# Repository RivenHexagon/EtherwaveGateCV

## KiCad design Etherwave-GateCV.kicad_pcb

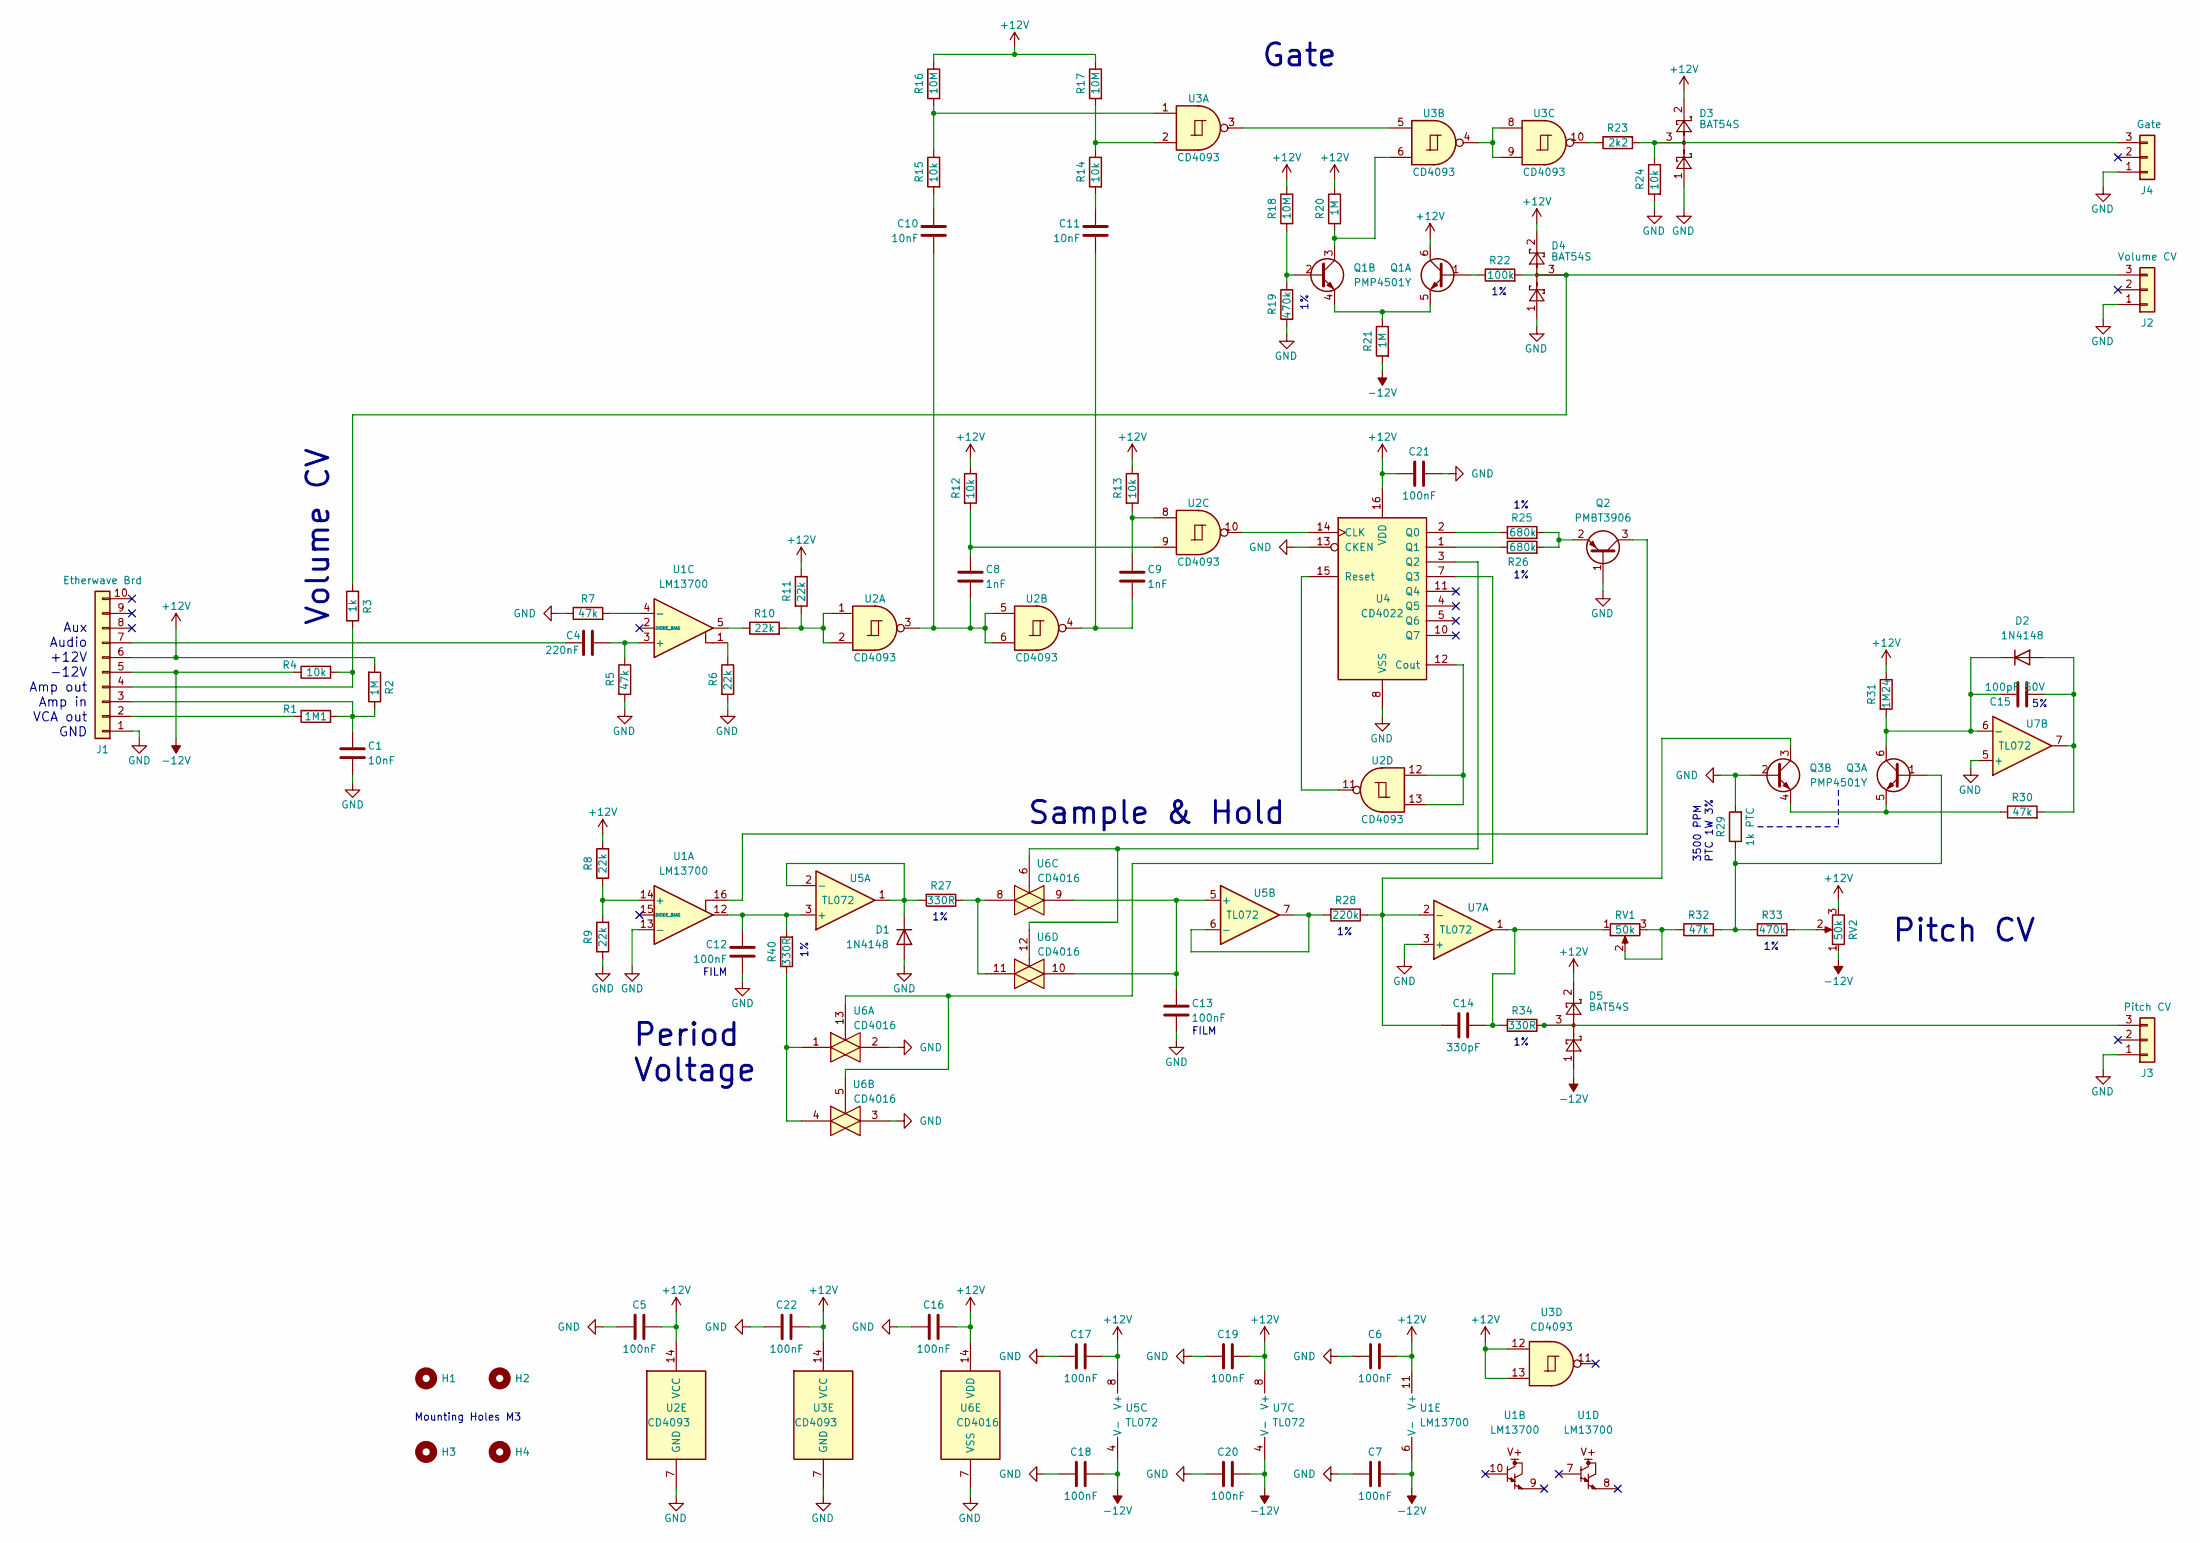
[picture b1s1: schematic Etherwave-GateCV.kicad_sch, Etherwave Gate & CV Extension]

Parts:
C1, C10, C11: 10nF; C_0603_1608Metric_Pad1.08x0.95mm_HandSolder
C4: 220nF; C_0603_1608Metric_Pad1.08x0.95mm_HandSolder
C5, C6, C7, C16, C17, C18, C19, C20, C21, C22: 100nF; C_0603_1608Metric_Pad1.08x0.95mm_HandSolder
C8, C9: 1nF; C_0603_1608Metric_Pad1.08x0.95mm_HandSolder
C12, C13: 100nF; C_1812_4532Metric_Pad1.57x3.40mm_HandSolder
C14: 330pF; C_0603_1608Metric_Pad1.08x0.95mm_HandSolder
C15: 100pF 50V; C_0603_1608Metric_Pad1.08x0.95mm_HandSolder
D1, D2: 1N4148; D_SOD-323_HandSoldering
D3, D4, D5: BAT54S; SOT-23
H1, H2, H3, H4: MountingHole; MountingHole_3.2mm_M3_DIN965
J1: Etherwave Brd; Molex_KK-254_AE-6410-10A_1x10_P2.54mm_Vertical
J2: Volume CV; Molex_KK-254_AE-6410-03A_1x03_P2.54mm_Vertical
J3: Pitch CV; Molex_KK-254_AE-6410-03A_1x03_P2.54mm_Vertical
J4: Gate; Molex_KK-254_AE-6410-03A_1x03_P2.54mm_Vertical
Q1, Q3: PMP4501Y; SOT-363_SC-70-6_Handsoldering
Q2: PMBT3906; SOT-23_Handsoldering
R1: 1M1; R_0603_1608Metric_Pad0.98x0.95mm_HandSolder
R2, R20, R21: 1M; R_0603_1608Metric_Pad0.98x0.95mm_HandSolder
R3: 1k; R_0603_1608Metric_Pad0.98x0.95mm_HandSolder
R4, R12, R13, R14, R15, R24: 10k; R_0603_1608Metric_Pad0.98x0.95mm_HandSolder
R5, R7, R30, R32: 47k; R_0603_1608Metric_Pad0.98x0.95mm_HandSolder
R6, R8, R9, R10, R11: 22k; R_0603_1608Metric_Pad0.98x0.95mm_HandSolder
R16, R17, R18: 10M; R_0603_1608Metric_Pad0.98x0.95mm_HandSolder
R19, R33: 470k; R_0603_1608Metric_Pad0.98x0.95mm_HandSolder
R22: 100k; R_0603_1608Metric_Pad0.98x0.95mm_HandSolder
R23: 2k2; R_0603_1608Metric_Pad0.98x0.95mm_HandSolder
R25, R26: 680k; R_0603_1608Metric_Pad0.98x0.95mm_HandSolder
R27, R34, R40: 330R; R_0603_1608Metric_Pad0.98x0.95mm_HandSolder
R28: 220k; R_0603_1608Metric_Pad0.98x0.95mm_HandSolder
R29: 1k PTC; R_0603_1608Metric_Pad0.98x0.95mm_HandSolder
R31: 1M24; R_0603_1608Metric_Pad0.98x0.95mm_HandSolder
RV1, RV2: 50k; Potentiometer_Bourns_3266Z_Horizontal
U1: LM13700; SOIC-16_3.9x9.9mm_P1.27mm
U2, U3: CD4093; TSSOP-14_4.4x5mm_P0.65mm
U4: CD4022; TSSOP-16_4.4x5mm_P0.65mm
U5, U7: TL072; SOIC-8_3.9x4.9mm_P1.27mm
U6: CD4016; SOIC-14_3.9x8.7mm_P1.27mm

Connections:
+12V: C5.2, C6.2, C16.2, C17.2, C19.2, C21.2, C22.2, D3.2, D4.2, D5.2, J1.6, Q1.6 (C1), R2.2, R8.2, R11.1, R12.1, R13.1, R16.1, R17.1, R18.1, R20.1, R31.1, RV2.3, U1.11 (V+), U2.14 (VCC), U3.12, U3.13, U3.14 (VCC), U4.16 (VDD), U5.8 (V+), U6.14 (VDD), U7.8 (V+)
-12V: C7.2, C18.2, C20.2, D5.1, J1.5, R4.1, R21.2, RV2.1, U1.6 (V-), U5.4 (V-), U7.4 (V-)
GND: C1.2, C5.1, C6.1, C7.1, C12.2, C13.2, C16.1, C17.1, C18.1, C19.1, C20.1, C21.1, C22.1, D1.2 (A), D3.1, D4.1, J1.1, J2.1, J3.1, J4.1, Q2.1 (B), Q3.2 (B2), R5.2, R6.2, R7.1, R9.1, R19.2, R24.2, R29.2, U1.13 (-), U2.7 (GND), U3.7 (GND), U4.8 (VSS), U4.13 (CKEN), U6.2, U6.3, U6.7 (VSS), U7.3 (+), U7.5 (+)
unnamed: C8.1, R12.2, U2.9
unnamed: C9.1, R13.2, U2.8
unnamed: C10.1, R15.2
unnamed: C8.2, C10.2, U2.3, U2.5, U2.6
unnamed: C11.1, R14.2
unnamed: C9.2, C11.2, U2.4
unnamed: C14.2, R34.2, RV1.1, U7.1
unnamed: D1.1 (K), R27.2, U5.1, U5.2 (-)
unnamed: C15.2, D2.2 (A), R30.2, U7.7
unnamed: C15.1, D2.1 (K), Q3.6 (C1), R31.2, U7.6 (-)
unnamed: J1.2, R1.1
unnamed: C1.1, J1.3, R1.2, R2.1
unnamed: J1.4, R3.1, R4.2
unnamed: C4.1, J1.7
unnamed: D4.3, J2.3, R3.2, R22.2
unnamed: D5.3, J3.3, R34.1
unnamed: D3.3, J4.3, R23.2, R24.1
unnamed: Q1.1 (B1), R22.1
unnamed: Q1.4 (E2), Q1.5 (E1), R21.1
unnamed: Q1.2 (B2), R18.2, R19.1
unnamed: Q1.3 (C2), R20.2, U3.6
unnamed: Q2.3 (C), U1.16
unnamed: Q2.2 (E), R25.2, R26.2
unnamed: Q3.1 (B1), R29.1, R32.2, R33.2
unnamed: Q3.4 (E2), Q3.5 (E1), R30.1
unnamed: C14.1, Q3.3 (C2), R28.1, U7.2 (-)
unnamed: R6.1, U1.1
unnamed: R10.1, U1.5
unnamed: R10.2, R11.2, U2.1, U2.2
unnamed: R14.1, R17.2, U3.2
unnamed: R15.1, R16.2, U3.1
unnamed: R23.1, U3.10
unnamed: R27.1, U6.8, U6.11
unnamed: R32.1, RV1.2, RV1.3
unnamed: R33.1, RV2.2
unnamed: R40.1, U6.1, U6.4
unnamed: R8.1, R9.2, U1.14 (+)
unnamed: C4.2, R5.1, U1.3 (+)
unnamed: R7.2, U1.4 (-)
unnamed: U3.3, U3.5
unnamed: U3.4, U3.8, U3.9
unnamed: U2.10, U4.14 (CLK)
unnamed: U2.12, U2.13, U4.12 (Cout)
unnamed: R25.1, U4.2 (Q0)
unnamed: R26.1, U4.1 (Q1)
unnamed: U4.3 (Q2), U6.6, U6.12
unnamed: U4.7 (Q3), U6.5, U6.13
unnamed: U2.11, U4.15 (Reset)
unnamed: C12.1, R40.2, U1.12, U5.3 (+)
unnamed: C13.1, U5.5 (+), U6.9, U6.10
unnamed: R28.2, U5.6 (-), U5.7

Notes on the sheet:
FILM
Sample & Hold
Aux Audio +12V -12V Amp out Amp in VCA out GND
Pitch CV
3500 PPM PTC 1W 3%
Mounting Holes M3
Gate
Period Voltage
Volume CV

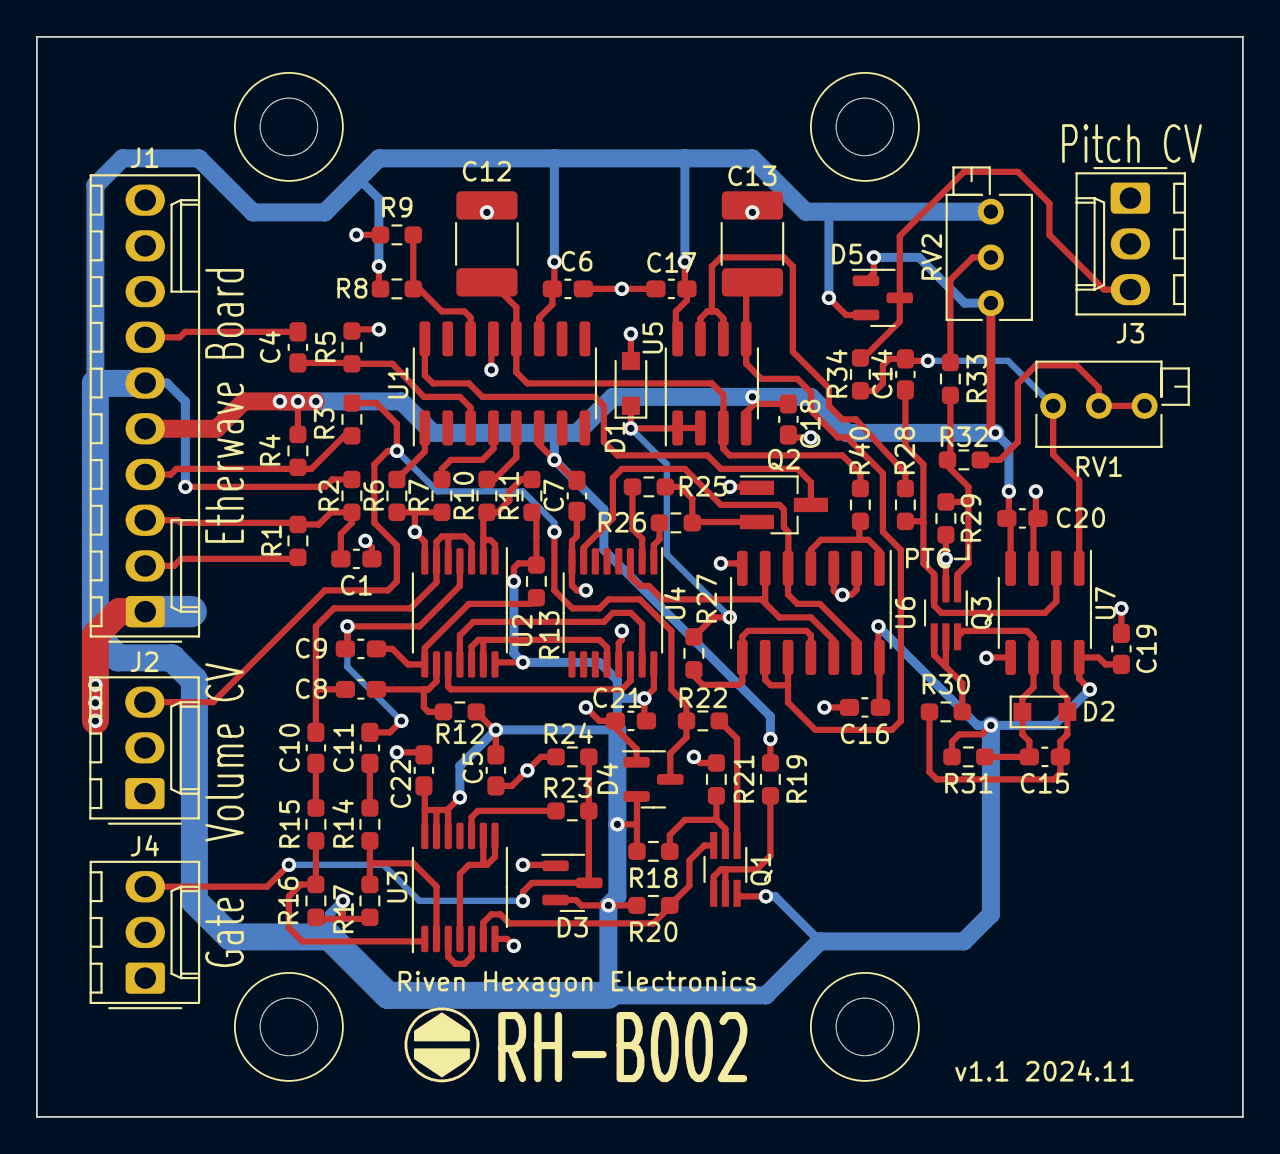
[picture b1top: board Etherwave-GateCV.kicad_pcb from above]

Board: 2 copper layers, 67.0 x 60.0 mm, 80 parts (0 on the bottom side), 54 nets.

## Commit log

2023-04-15 placed all semiconductors on schematic
2023-04-15 annotation for semiconductors
2023-04-15 footprint assignment for semiconductors
2023-04-15 placed Volume CV Circuit
2023-04-16 placed power section and started with circuit from Audio in
2023-04-16 completed pulse discriminator network
2023-04-16 completed gate circuit
2023-04-16 replaced circuits
2023-04-16 completed counter circuit
2023-04-16 completed control circuit
2023-04-16 circuit completed
2023-05-07 completed footprint assignment
2023-05-07 changed some special device footprint (C12, C13), created board file
2023-05-07 about 40 % layout done
2023-05-08 2/3 of layout
2023-05-10 done top layer routing
2023-05-12 ready for power distribution
2023-05-12 -12 routing done, part of +12 V
2023-05-12 power routing completed
2023-05-12 silk screen done and mountiong holes placed
2023-05-12 added mounting holes
2023-05-12 PCB ordered at JLCPCB
2023-05-18 factory output, BOM, assembly
2024-11-30 added missing connection U7-A-1, C14, P1-1, R14. replaces hotfix
